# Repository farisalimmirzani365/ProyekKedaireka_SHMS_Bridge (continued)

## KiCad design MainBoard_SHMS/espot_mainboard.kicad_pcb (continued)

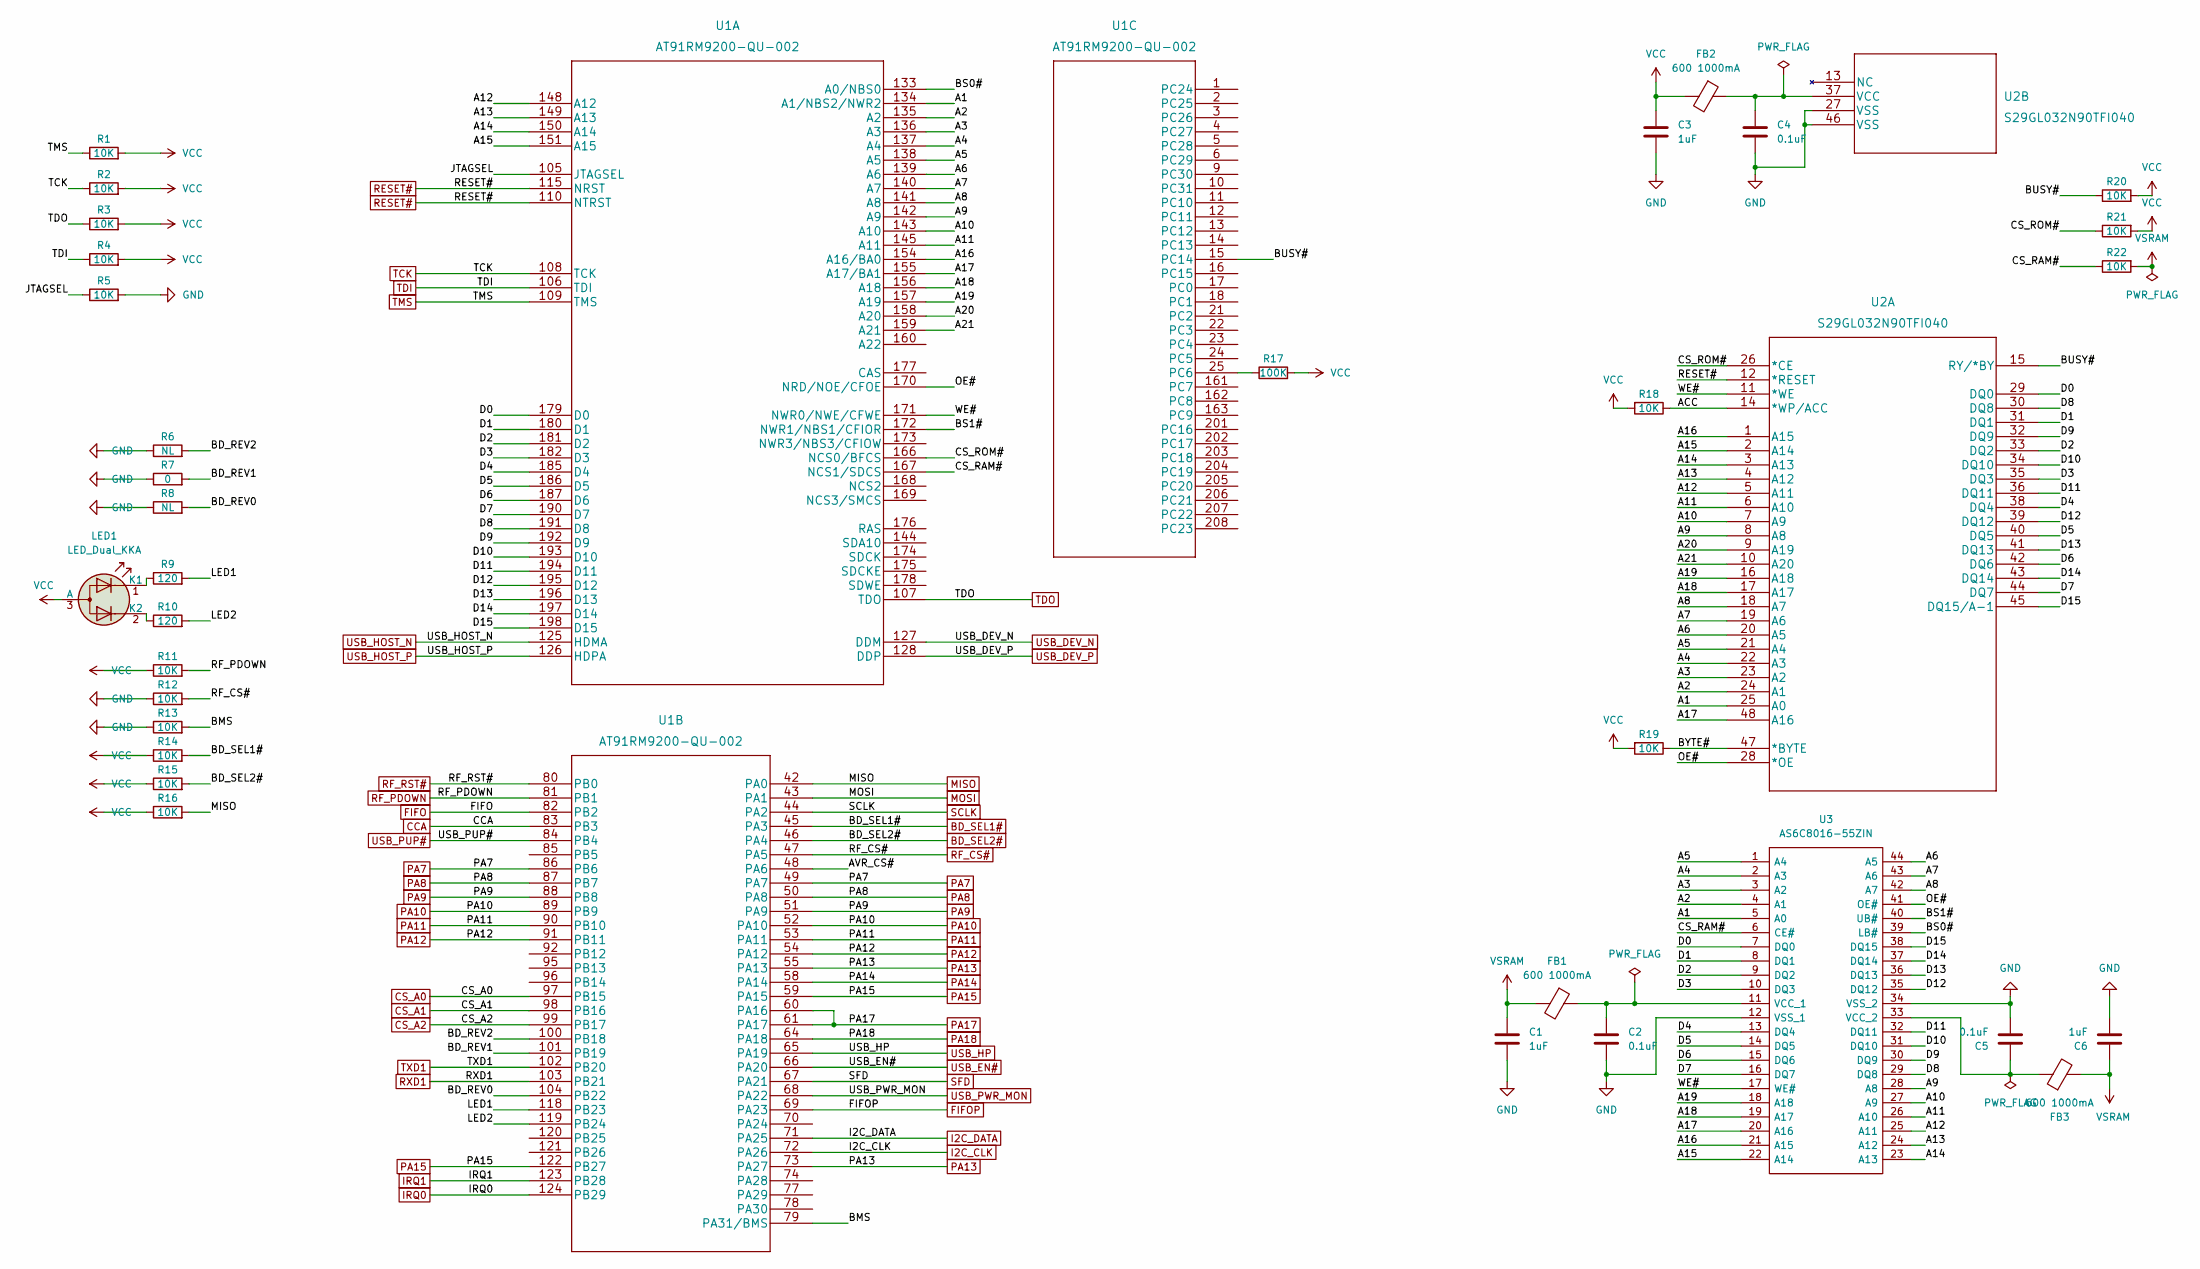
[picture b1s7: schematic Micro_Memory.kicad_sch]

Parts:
C1, C3, C6: 1uF; C_0603_1608Metric_Pad1.08x0.95mm_HandSolder
C2, C4, C5: 0.1uF; C_0603_1608Metric_Pad1.08x0.95mm_HandSolder
FB1, FB2, FB3: 600 1000mA; L_0603_1608Metric_Pad1.05x0.95mm_HandSolder
LED1: LED_Dual_KKA; LED_LiteOn_LTST-S326
R1, R2, R3, R4, R5, R11, R12, R13, R14, R15, R16, R18, R19, R20, R21, R22: 10K; R_0603_1608Metric_Pad0.98x0.95mm_HandSolder
R6, R8: NL; R_0603_1608Metric_Pad0.98x0.95mm_HandSolder
R7: 0; R_0603_1608Metric_Pad0.98x0.95mm_HandSolder
R9, R10: 120; R_0603_1608Metric_Pad0.98x0.95mm_HandSolder
R17: 100K; R_0603_1608Metric_Pad0.98x0.95mm_HandSolder
U1: AT91RM9200-QU-002; PQFP208_ATM
U2: S29GL032N90TFI040; TS048_SPA
U3: AS6C8016-55ZIN; SOP80P1176X120-44N; Manufacturer_Part_Number AS6C8016-55ZIN; Mouser Part Number 913-AS6C8016-55ZIN

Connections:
/Micro Memory/A1: U1.134 (A1/NBS2/NWR2), U2.25 (A0), U3.5 (A0)
/Micro Memory/A2: U1.135 (A2), U2.24 (A1), U3.4 (A1)
/Micro Memory/A3: U1.136 (A3), U2.23 (A2), U3.3 (A2)
/Micro Memory/A4: U1.137 (A4), U2.22 (A3), U3.2 (A3)
/Micro Memory/A5: U1.138 (A5), U2.21 (A4), U3.1 (A4)
/Micro Memory/A6: U1.139 (A6), U2.20 (A5), U3.44 (A5)
/Micro Memory/A7: U1.140 (A7), U2.19 (A6), U3.43 (A6)
/Micro Memory/A8: U1.141 (A8), U2.18 (A7), U3.42 (A7)
/Micro Memory/A9: U1.142 (A9), U2.8 (A8), U3.28 (A8)
/Micro Memory/A10: U1.143 (A10), U2.7 (A9), U3.27 (A9)
/Micro Memory/A11: U1.145 (A11), U2.6 (A10), U3.26 (A10)
/Micro Memory/A12: U1.148 (A12), U2.5 (A11), U3.25 (A11)
/Micro Memory/A13: U1.149 (A13), U2.4 (A12), U3.24 (A12)
/Micro Memory/A14: U1.150 (A14), U2.3 (A13), U3.23 (A13)
/Micro Memory/A15: U1.151 (A15), U2.2 (A14), U3.22 (A14)
/Micro Memory/A16: U1.154 (A16/BA0), U2.1 (A15), U3.21 (A15)
/Micro Memory/A17: U1.155 (A17/BA1), U2.48 (A16), U3.20 (A16)
/Micro Memory/A18: U1.156 (A18), U2.17 (A17), U3.19 (A17)
/Micro Memory/A19: U1.157 (A19), U2.16 (A18), U3.18 (A18)
/Micro Memory/A20: U1.158 (A20), U2.9 (A19)
/Micro Memory/A21: U1.159 (A21), U2.10 (A20)
/Micro Memory/ACC: R18.1, U2.14 (*WP/ACC)
/Micro Memory/AVR_CS#: U1.48 (PA6)
/Micro Memory/BD_REV0: R8.2, U1.104 (PB22)
/Micro Memory/BD_REV1: R7.2, U1.101 (PB19)
/Micro Memory/BD_REV2: R6.2, U1.100 (PB18)
/Micro Memory/BMS: R13.2, U1.79 (PA31/BMS)
/Micro Memory/BS0#: U1.133 (A0/NBS0), U3.39 (LB#)
/Micro Memory/BS1#: U1.172 (NWR1/NBS1/CFIOR), U3.40 (UB#)
/Micro Memory/BUSY#: R20.1, U1.15 (PC14), U2.15 (RY/*BY)
/Micro Memory/BYTE#: R19.1, U2.47 (*BYTE)
/Micro Memory/CS_RAM#: R22.1, U1.167 (NCS1/SDCS), U3.6 (CE#)
/Micro Memory/CS_ROM#: R21.1, U1.166 (NCS0/BFCS), U2.26 (*CE)
/Micro Memory/D0: U1.179 (D0), U2.29 (DQ0), U3.7 (DQ0)
/Micro Memory/D1: U1.180 (D1), U2.31 (DQ1), U3.8 (DQ1)
/Micro Memory/D2: U1.181 (D2), U2.33 (DQ2), U3.9 (DQ2)
/Micro Memory/D3: U1.182 (D3), U2.35 (DQ3), U3.10 (DQ3)
/Micro Memory/D4: U1.185 (D4), U2.38 (DQ4), U3.13 (DQ4)
/Micro Memory/D5: U1.186 (D5), U2.40 (DQ5), U3.14 (DQ5)
/Micro Memory/D6: U1.187 (D6), U2.42 (DQ6), U3.15 (DQ6)
/Micro Memory/D7: U1.190 (D7), U2.44 (DQ7), U3.16 (DQ7)
/Micro Memory/D8: U1.191 (D8), U2.30 (DQ8), U3.29 (DQ8)
/Micro Memory/D9: U1.192 (D9), U2.32 (DQ9), U3.30 (DQ9)
/Micro Memory/D10: U1.193 (D10), U2.34 (DQ10), U3.31 (DQ10)
/Micro Memory/D11: U1.194 (D11), U2.36 (DQ11), U3.32 (DQ11)
/Micro Memory/D12: U1.195 (D12), U2.39 (DQ12), U3.35 (DQ12)
/Micro Memory/D13: U1.196 (D13), U2.41 (DQ13), U3.36 (DQ13)
/Micro Memory/D14: U1.197 (D14), U2.43 (DQ14), U3.37 (DQ14)
/Micro Memory/D15: U1.198 (D15), U2.45 (DQ15/A-1), U3.38 (DQ15)
/Micro Memory/JTAGSEL: R5.1, U1.105 (JTAGSEL)
/Micro Memory/LED1: R9.2, U1.118 (PB23)
/Micro Memory/LED2: R10.2, U1.119 (PB24)
/Micro Memory/OE#: U1.170 (NRD/NOE/CFOE), U2.28 (*OE), U3.41 (OE#)
/Micro Memory/WE#: U1.171 (NWR0/NWE/CFWE), U2.11 (*WE), U3.17 (WE#)
BD_SEL1#: R14.2, U1.45 (PA3); also elsewhere on the board
BD_SEL2#: R15.2, U1.46 (PA4); also elsewhere on the board
CCA: U1.83 (PB3); also elsewhere on the board
CS_A0: U1.97 (PB15); also elsewhere on the board
CS_A1: U1.98 (PB16); also elsewhere on the board
CS_A2: U1.99 (PB17); also elsewhere on the board
FIFO: U1.82 (PB2); also elsewhere on the board
FIFOP: U1.69 (PA23); also elsewhere on the board
GND: C1.2, C2.2, C3.2, C4.2, C5.2, C6.2, R5.2, R6.1, R7.1, R8.1, R12.1, R13.1, U2.27 (VSS), U2.46 (VSS), U3.12 (VSS_1), U3.34 (VSS_2); also elsewhere on the board
I2C_CLK: U1.72 (PA26); also elsewhere on the board
I2C_DATA: U1.71 (PA25); also elsewhere on the board
IRQ0: U1.124 (PB29); also elsewhere on the board
IRQ1: U1.123 (PB28); also elsewhere on the board
MISO: R16.2, U1.42 (PA0); also elsewhere on the board
MOSI: U1.43 (PA1); also elsewhere on the board
unnamed: C2.1, FB1.1, U3.11 (VCC_1)
unnamed: C4.1, FB2.1, U2.37 (VCC)
unnamed: C5.1, FB3.1, U3.33 (VCC_2)
unnamed: LED1.1 (K1), R9.1
unnamed: LED1.2 (K2), R10.1
unnamed: R17.1, U1.25 (PC6)
PA7: U1.49 (PA7), U1.86 (PB6); also elsewhere on the board
PA8: U1.50 (PA8), U1.87 (PB7); also elsewhere on the board
PA9: U1.51 (PA9), U1.88 (PB8); also elsewhere on the board
PA10: U1.52 (PA10), U1.89 (PB9); also elsewhere on the board
PA11: U1.53 (PA11), U1.90 (PB10); also elsewhere on the board
PA12: U1.54 (PA12), U1.91 (PB11); also elsewhere on the board
PA13: U1.55 (PA13), U1.73 (PA27); also elsewhere on the board
PA14: U1.58 (PA14); also elsewhere on the board
PA15: U1.59 (PA15), U1.122 (PB27); also elsewhere on the board
PA17: U1.60 (PA16), U1.61 (PA17); also elsewhere on the board
PA18: U1.64 (PA18); also elsewhere on the board
RESET#: U1.110 (NTRST), U1.115 (NRST), U2.12 (*RESET); also elsewhere on the board
RF_CS#: R12.2, U1.47 (PA5); also elsewhere on the board
RF_PDOWN: R11.2, U1.81 (PB1); also elsewhere on the board
RF_RST#: U1.80 (PB0); also elsewhere on the board
RXD1: U1.103 (PB21); also elsewhere on the board
SCLK: U1.44 (PA2); also elsewhere on the board
SFD: U1.67 (PA21); also elsewhere on the board
TCK: R2.1, U1.108 (TCK); also elsewhere on the board
TDI: R4.1, U1.106 (TDI); also elsewhere on the board
TDO: R3.1, U1.107 (TDO); also elsewhere on the board
TMS: R1.1, U1.109 (TMS); also elsewhere on the board
TXD1: U1.102 (PB20); also elsewhere on the board
USB_DEV_N: U1.127 (DDM); also elsewhere on the board
USB_DEV_P: U1.128 (DDP); also elsewhere on the board
USB_EN#: U1.66 (PA20); also elsewhere on the board
USB_HOST_N: U1.125 (HDMA); also elsewhere on the board
USB_HOST_P: U1.126 (HDPA); also elsewhere on the board
USB_HP: U1.65 (PA19); also elsewhere on the board
USB_PUP#: U1.84 (PB4); also elsewhere on the board
USB_PWR_MON: U1.68 (PA22); also elsewhere on the board
VCC: C3.1, FB2.2, LED1.3 (A), R1.2, R2.2, R3.2, R4.2, R11.1, R14.1, R15.1, R16.1, R17.2, R18.2, R19.2, R20.2, R21.2; also elsewhere on the board
VSRAM: C1.1, C6.1, FB1.2, FB3.2, R22.2; also elsewhere on the board

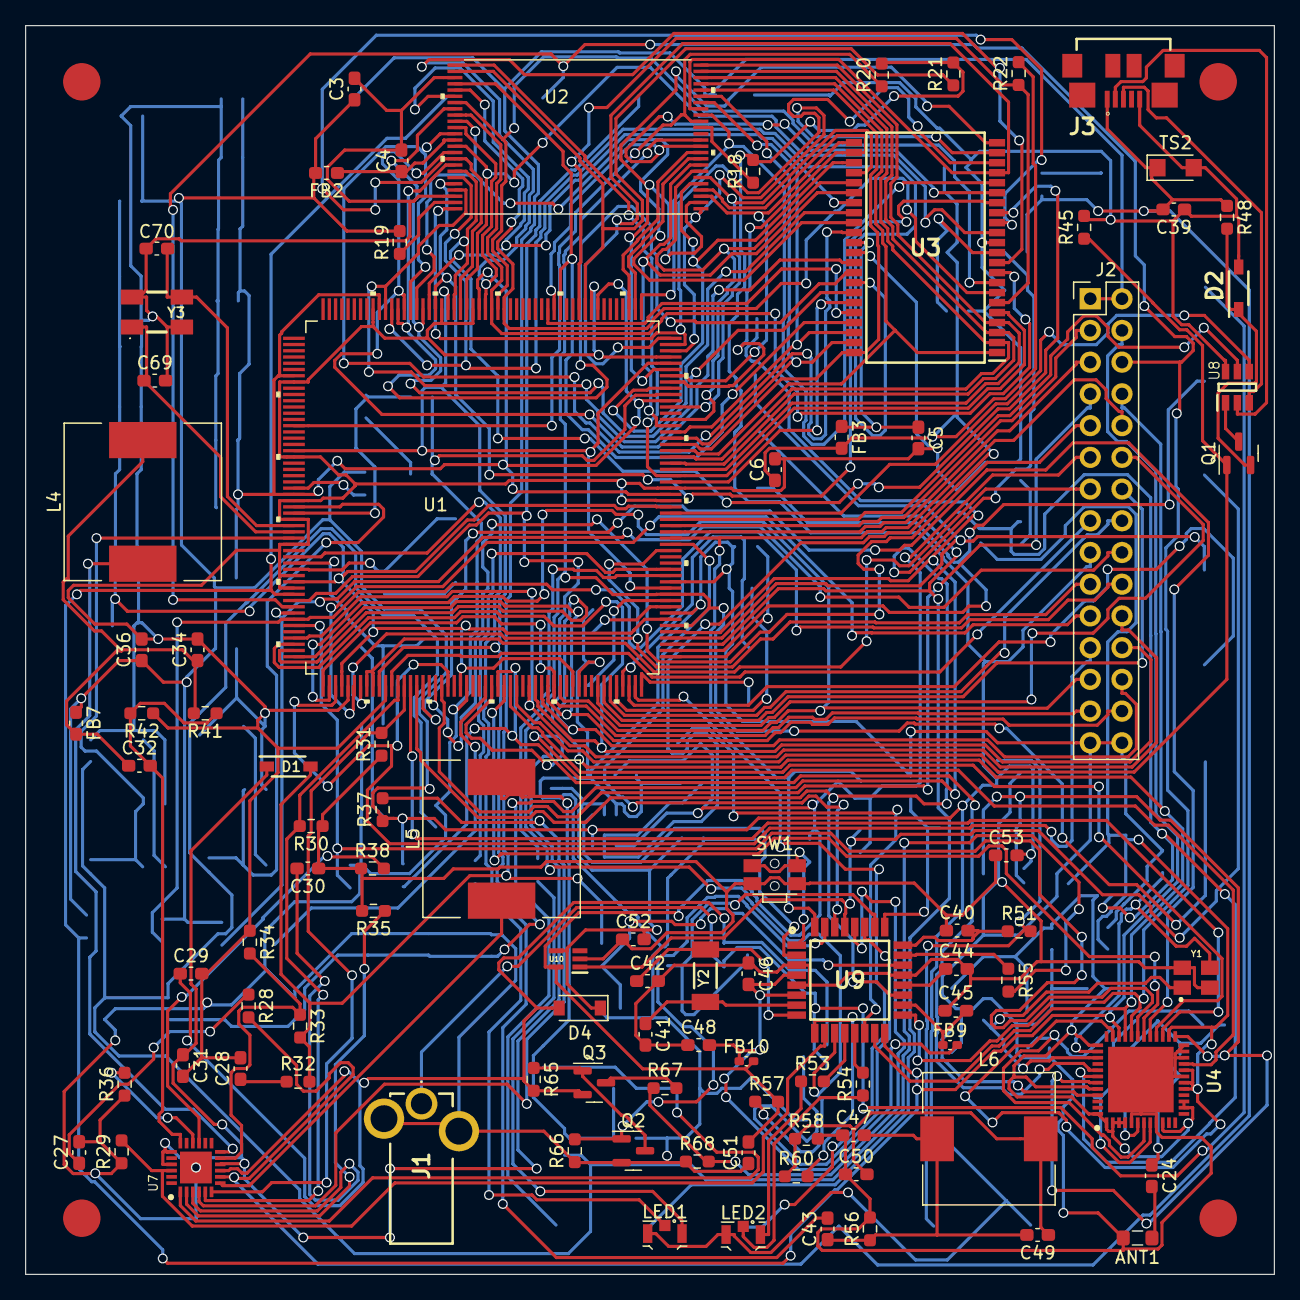
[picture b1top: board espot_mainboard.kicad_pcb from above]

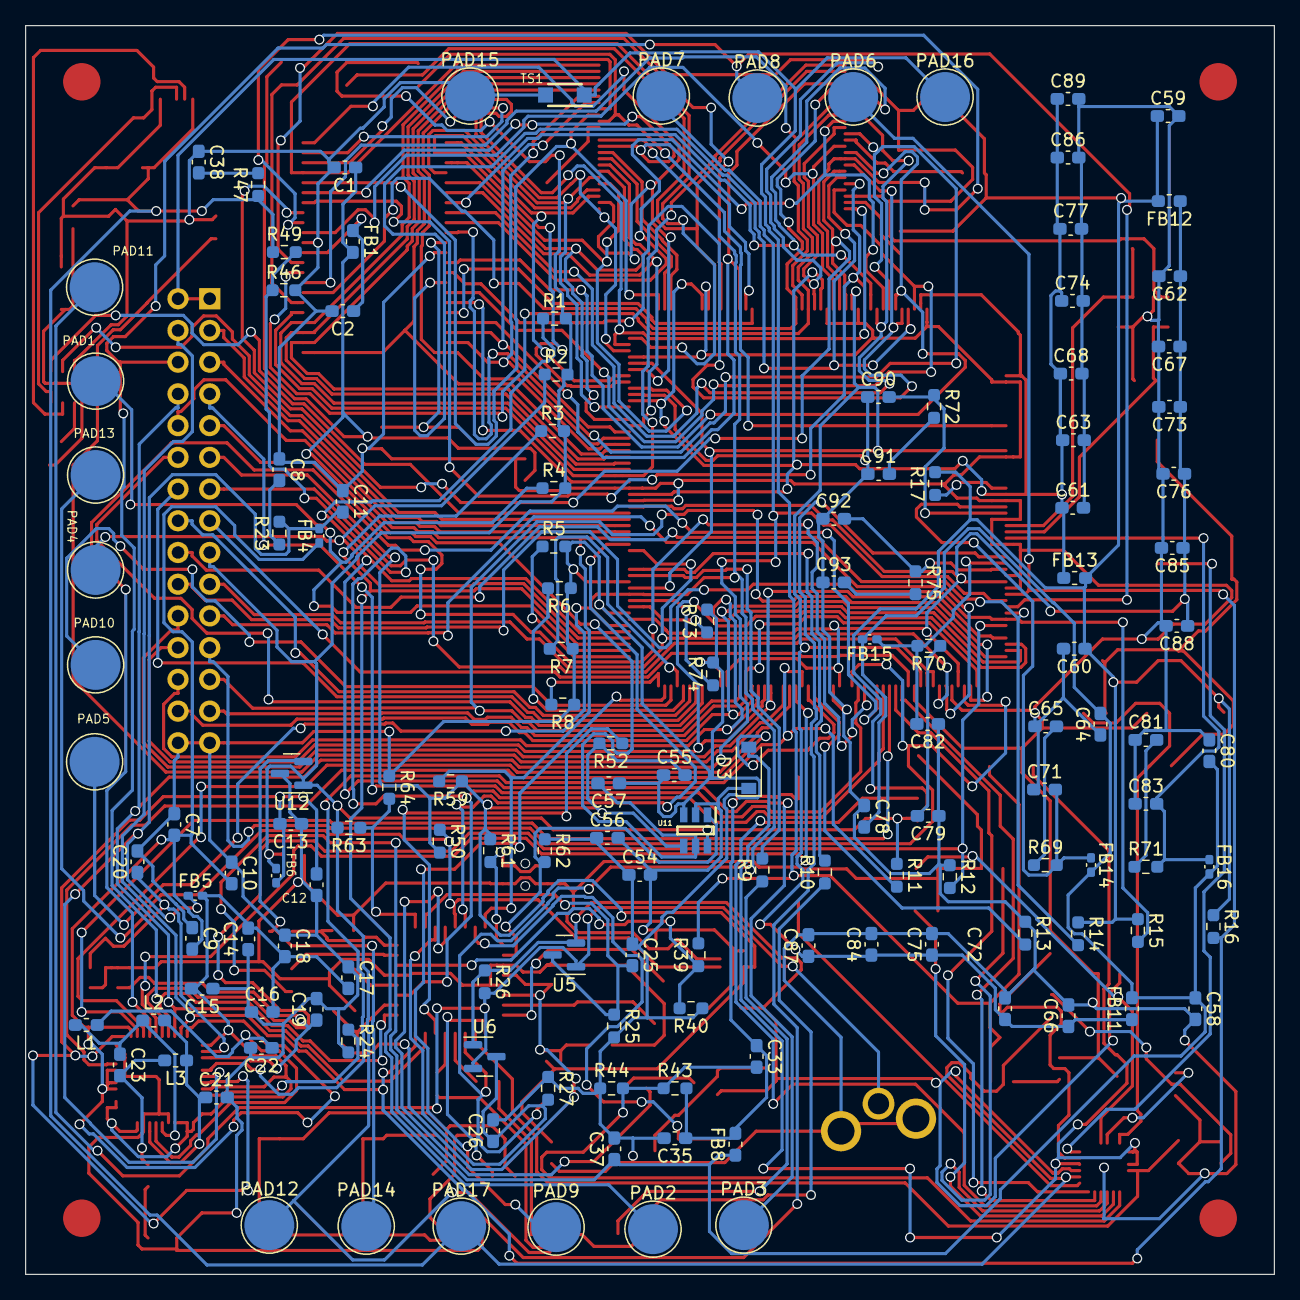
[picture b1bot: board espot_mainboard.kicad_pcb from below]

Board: 2 copper layers, 100.0 x 100.0 mm, 238 parts (143 on the bottom side), 193 nets.

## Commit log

2023-04-03 MainBoard_SHMS
2023-04-03 ANT-F
